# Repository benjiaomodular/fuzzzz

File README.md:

### References
- [Electrosmash fuzz face analysis](https://www.electrosmash.com/fuzz-face)

### Possible mods
- [Wacky Fuzz Face Mods](https://www.reddit.com/r/diypedals/comments/84mx70/wacky_fuzz_face_mods/)
- [JHS bias and volume mods](https://www.youtube.com/watch?v=ghxwcSiY7GQ)

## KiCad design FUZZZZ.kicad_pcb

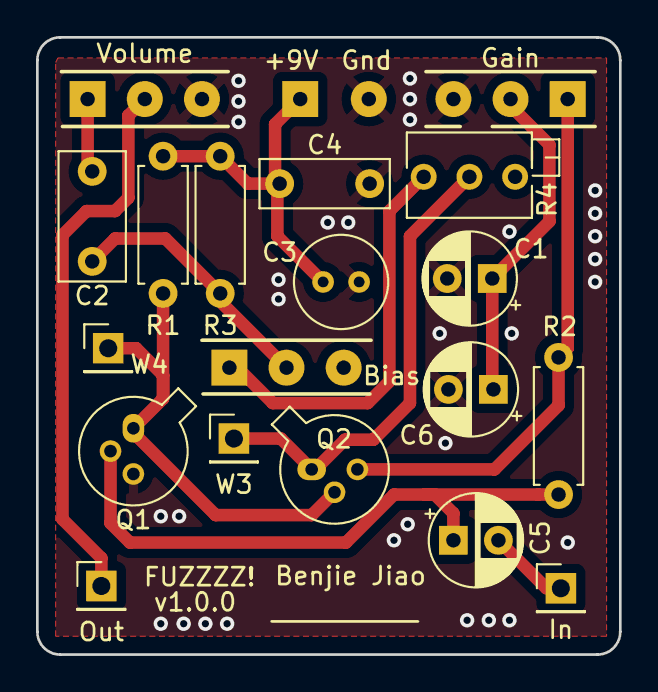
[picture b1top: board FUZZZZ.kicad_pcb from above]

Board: 2 copper layers, 32.4 x 34.3 mm, 20 parts (0 on the bottom side), 12 nets.

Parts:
+9V: Jack-DC; SolderWirePad_1x02_P3.81mm_Drill0.8mm
Bias: B10K; SolderWirePad_1x03_P3.175mm_Drill0.8mm
C1, C6: 10uF; CP_Radial_D5.0mm_P2.50mm
C2: 10nF; C_Rect_L7.0mm_W3.5mm_P5.00mm
C3: 10uF; C_Radial_D5.0mm_H5.0mm_P2.00mm
C4: 100nF; C_Rect_L7.0mm_W2.5mm_P5.00mm
C5: 2.2.uF; CP_Radial_D5.0mm_P2.50mm
Gain: B1K; SolderWirePad_1x03_P3.175mm_Drill0.8mm
In: AUDIO IN; PinHeader_1x01_P2.54mm_Vertical
Out: AUDIO OUT; PinHeader_1x01_P2.54mm_Vertical
Q1, Q2: BC108; TO-18-3
R1: 33K; R_Axial_DIN0207_L6.3mm_D2.5mm_P7.62mm_Horizontal
R2: 100K; R_Axial_DIN0207_L6.3mm_D2.5mm_P7.62mm_Horizontal
R3: 330; R_Axial_DIN0207_L6.3mm_D2.5mm_P7.62mm_Horizontal
R4: 10K; Potentiometer_Bourns_3266Z_Horizontal
Volume: A500K; SolderWirePad_1x03_P3.175mm_Drill0.8mm
W3, W4: TEST_1P; PinHeader_1x01_P2.54mm_Vertical

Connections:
+9V: +9V.1, C3.1, C4.1, R1.1, R3.2
Earth: +9V.2, C1.2, C3.2, C4.2, C6.2, Gain.3, Q1.3, Volume.3
unnamed: Bias.1, R4.1
unnamed: Bias.2, C2.1, R3.1
unnamed: C1.1, C6.1, Gain.2
unnamed: C2.2, Volume.1
unnamed: C5.1, Q1.2, R2.2
unnamed: C5.2, In.1
unnamed: Gain.1, Q2.3, R2.1
unnamed: Q1.1, Q2.2, R1.2, W4.1
unnamed: Q2.1, R4.2, W3.1
unnamed: Out.1, Volume.2

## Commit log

2020-10-17 hello git
2020-10-17 Added readme
2020-11-04 Some corrections after first PCB
2023-12-05 Updated bom
